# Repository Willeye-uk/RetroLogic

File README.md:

# **The RetroLogic 6502 SBC - KiCad 9 Files ([Ben Eater](https://eater.net/6502) Inspired)**

---

Welcome to the repository for the **KiCad 9 design files** of a single board computer (SBC) based on the classic **W65C02S microprocessor**. This project draws heavy inspiration from [Ben Eater's excellent 6502 computer series](https://eater.net/6502), expanding upon it with a range of features for greater versatility and modern connectivity.

## **Features**

This SBC design aims to provide a robust platform for learning and experimenting with the 6502. Key features include:

* **W65C02S Processor:** Capable of running up to **14 MHz**.
* **Memory:**
    * **62256 SRAM:** For fast read/write memory operations.
    * **28C256 EEPROM:** For storing your programs and firmware.
* **Input/Output:**
    * **65C22 Versatile Interface Adapter (VIA):** Provides programmable parallel I/O, timers, and shift registers.
    * **65C51 Asynchronous Communications Interface Adapter (ACIA):** For serial communication capabilities.
* **Connectivity:**
    * **DB9 Serial Port:** Standard serial connector for PC communication (via MAX232 level shifter).
    * **FTDI Breakout Serial Socket:** Convenient header for connecting an FTDI serial-to-USB adapter.
    * **SD Card Socket:** For mass storage, enabling easier program loading and data logging.
    * **LCD Screen Connector:** Directly interface with character LCDs.
* **Power & Expansion:**
    * **USB-B Power Socket:** Modern and widely available power input.
    * **Power Switch:** For easy power control.
    * **Crystal Socket:** Flexible clocking options, allowing for different crystal frequencies.
    * **Switchable Voltage for Add-ons:** Provides configurable power for external modules and expansion boards.
    * **Expansion Port:** Example diagnostic board included.
    
    * **Sound Card:** Expansion sound card and demo program.
    
    * **Terminal Card:** Expansion VGA terminal based on https://geoffg.net/terminal.html

## **Getting Started**

To explore or modify this design, you'll need **KiCad 9**.

**Clone this repository: \
** Bash \
git clone https://github.com/Willeye-uk/RetroLogic.git

1. 
2. **Open the project in KiCad 9:** Navigate to the cloned directory and open the `.kicad_pro` file.

From there, you can view the schematics, examine the PCB layout, and generate manufacturing files if you wish to build your own board. Or use the ones provided in Gerber Files dir.

## **Contributing**

Contributions are welcome! If you find issues, have suggestions for improvements, or want to add features, feel free to open an issue or submit a pull request.

## **License**

This project is open-source. Please refer to the `LICENSE` file (if present) for details.

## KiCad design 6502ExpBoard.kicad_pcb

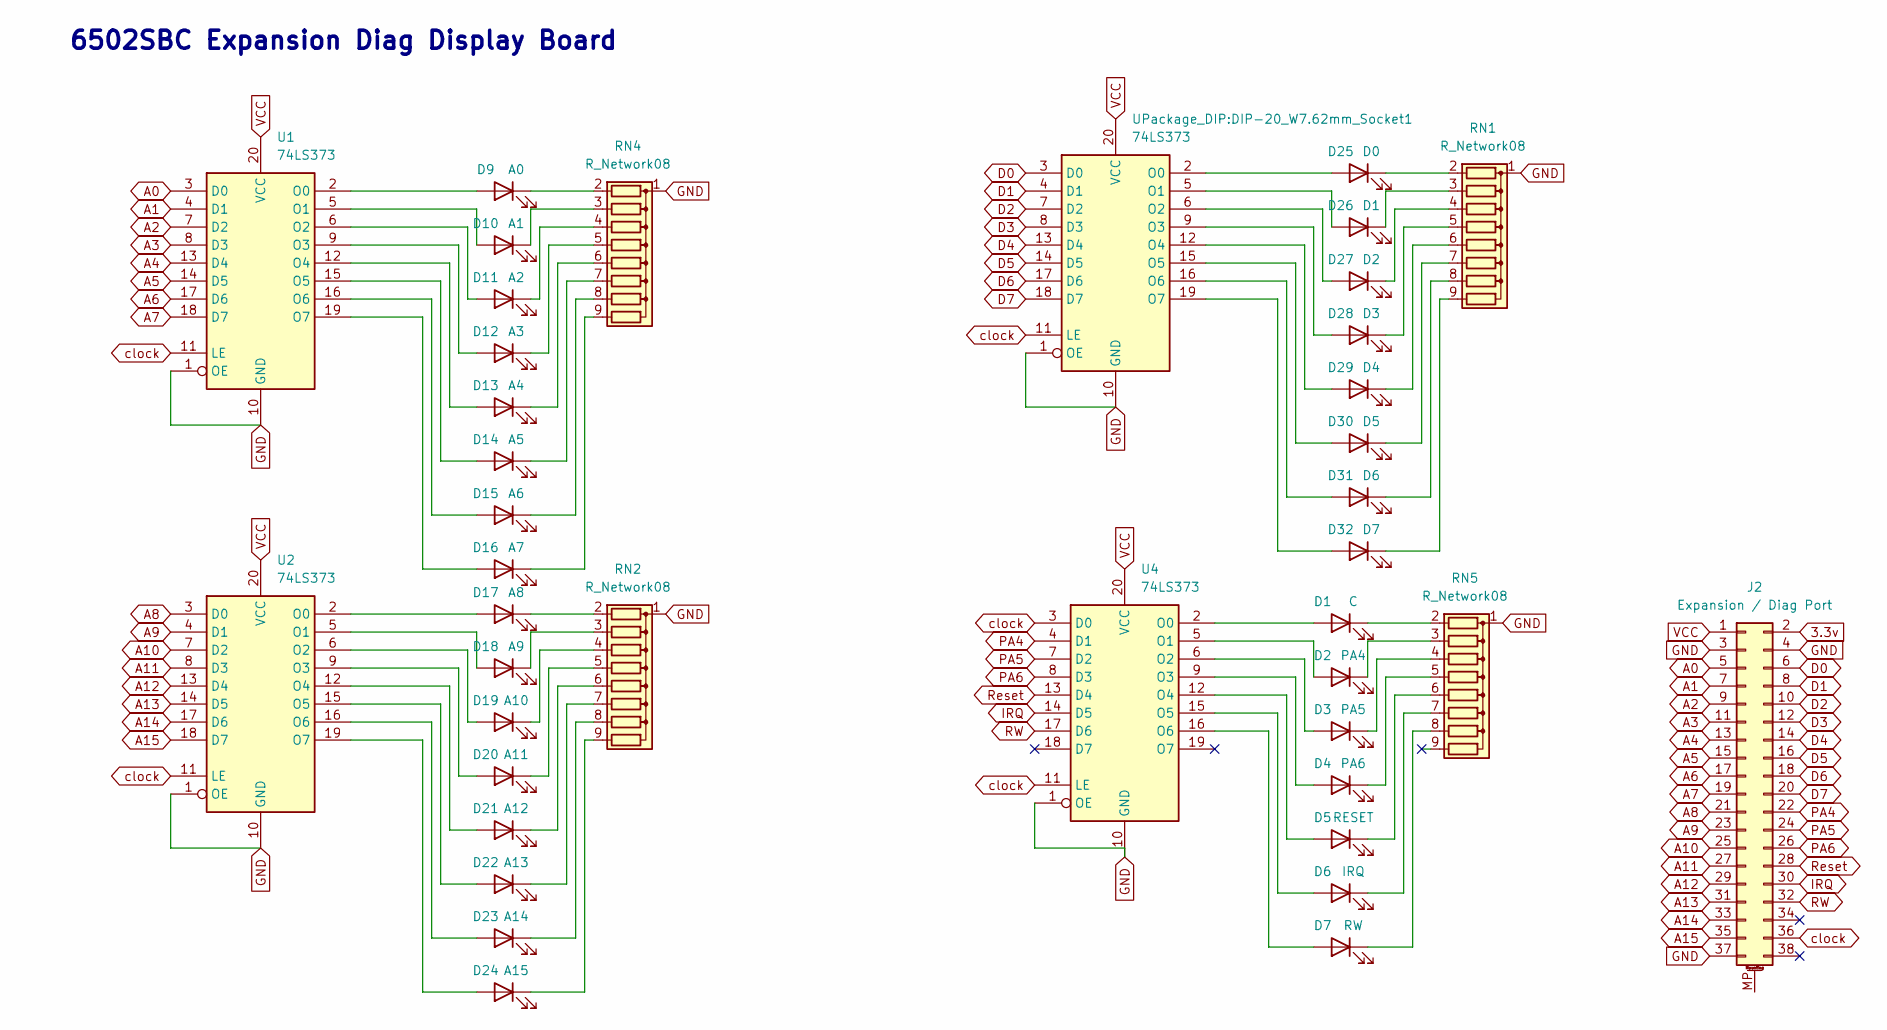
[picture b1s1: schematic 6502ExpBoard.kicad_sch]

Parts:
D1: C; LED_D3.0mm
D2: PA4; LED_D3.0mm
D3: PA5; LED_D3.0mm
D4: PA6; LED_D3.0mm
D5: RESET; LED_D3.0mm
D6: IRQ; LED_D3.0mm
D7: RW; LED_D3.0mm
D9: A0; LED_D3.0mm
D10: A1; LED_D3.0mm
D11: A2; LED_D3.0mm
D12: A3; LED_D3.0mm
D13: A4; LED_D3.0mm
D14: A5; LED_D3.0mm
D15: A6; LED_D3.0mm
D16: A7; LED_D3.0mm
D17: A8; LED_D3.0mm
D18: A9; LED_D3.0mm
D19: A10; LED_D3.0mm
D20: A11; LED_D3.0mm
D21: A12; LED_D3.0mm
D22: A13; LED_D3.0mm
D23: A14; LED_D3.0mm
D24: A15; LED_D3.0mm
D25: D0; LED_D3.0mm
D26: D1; LED_D3.0mm
D27: D2; LED_D3.0mm
D28: D3; LED_D3.0mm
D29: D4; LED_D3.0mm
D30: D5; LED_D3.0mm
D31: D6; LED_D3.0mm
D32: D7; LED_D3.0mm
J2: Expansion / Diag Port; PinHeader_2x19_P2.54mm_Vertical
RN1, RN2, RN4, RN5: R_Network08; R_Array_SIP9
U1, U2, U4: 74LS373; DIP-20_W7.62mm_Socket
UPackage_DIP:DIP-20_W7.62mm_Socket1: 74LS373; DIP-20_W7.62mm_Socket

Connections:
3.3v: J2.2
A0: J2.5, U1.3 (D0)
A1: J2.7, U1.4 (D1)
A2: J2.9, U1.7 (D2)
A3: J2.11, U1.8 (D3)
A4: J2.13, U1.13 (D4)
A5: J2.15, U1.14 (D5)
A6: J2.17, U1.17 (D6)
A7: J2.19, U1.18 (D7)
A8: J2.21, U2.3 (D0)
A9: J2.23, U2.4 (D1)
A10: J2.25, U2.7 (D2)
A11: J2.27, U2.8 (D3)
A12: J2.29, U2.13 (D4)
A13: J2.31, U2.14 (D5)
A14: J2.33, U2.17 (D6)
A15: J2.35, U2.18 (D7)
D0: J2.6, UPackage_DIP:DIP-20_W7.62mm_Socket1.3 (D0)
D1: J2.8, UPackage_DIP:DIP-20_W7.62mm_Socket1.4 (D1)
D2: J2.10, UPackage_DIP:DIP-20_W7.62mm_Socket1.7 (D2)
D3: J2.12, UPackage_DIP:DIP-20_W7.62mm_Socket1.8 (D3)
D4: J2.14, UPackage_DIP:DIP-20_W7.62mm_Socket1.13 (D4)
D5: J2.16, UPackage_DIP:DIP-20_W7.62mm_Socket1.14 (D5)
D6: J2.18, UPackage_DIP:DIP-20_W7.62mm_Socket1.17 (D6)
D7: J2.20, UPackage_DIP:DIP-20_W7.62mm_Socket1.18 (D7)
GND: J2.3, J2.4, J2.37, RN1.1 (common), RN2.1 (common), RN4.1 (common), RN5.1 (common), U1.1 (OE), U1.10 (GND), U2.1 (OE), U2.10 (GND), U4.1 (OE), U4.10 (GND), UPackage_DIP:DIP-20_W7.62mm_Socket1.1 (OE), UPackage_DIP:DIP-20_W7.62mm_Socket1.10 (GND)
IRQ: J2.30, U4.14 (D5)
unnamed: D1.2 (A), U4.2 (O0)
unnamed: D1.1 (K), RN5.2 (R1)
unnamed: D2.2 (A), U4.5 (O1)
unnamed: D2.1 (K), RN5.3 (R2)
unnamed: D3.2 (A), U4.6 (O2)
unnamed: D3.1 (K), RN5.4 (R3)
unnamed: D4.2 (A), U4.9 (O3)
unnamed: D4.1 (K), RN5.5 (R4)
unnamed: D5.2 (A), U4.12 (O4)
unnamed: D5.1 (K), RN5.6 (R5)
unnamed: D6.2 (A), U4.15 (O5)
unnamed: D6.1 (K), RN5.7 (R6)
unnamed: D7.2 (A), U4.16 (O6)
unnamed: D7.1 (K), RN5.8 (R7)
unnamed: D9.2 (A), U1.2 (O0)
unnamed: D9.1 (K), RN4.2 (R1)
unnamed: D10.2 (A), U1.5 (O1)
unnamed: D10.1 (K), RN4.3 (R2)
unnamed: D11.2 (A), U1.6 (O2)
unnamed: D11.1 (K), RN4.4 (R3)
unnamed: D12.2 (A), U1.9 (O3)
unnamed: D12.1 (K), RN4.5 (R4)
unnamed: D13.2 (A), U1.12 (O4)
unnamed: D13.1 (K), RN4.6 (R5)
unnamed: D14.2 (A), U1.15 (O5)
unnamed: D14.1 (K), RN4.7 (R6)
unnamed: D15.2 (A), U1.16 (O6)
unnamed: D15.1 (K), RN4.8 (R7)
unnamed: D16.2 (A), U1.19 (O7)
unnamed: D16.1 (K), RN4.9 (R8)
unnamed: D17.2 (A), U2.2 (O0)
unnamed: D17.1 (K), RN2.2 (R1)
unnamed: D18.2 (A), U2.5 (O1)
unnamed: D18.1 (K), RN2.3 (R2)
unnamed: D19.2 (A), U2.6 (O2)
unnamed: D19.1 (K), RN2.4 (R3)
unnamed: D20.2 (A), U2.9 (O3)
unnamed: D20.1 (K), RN2.5 (R4)
unnamed: D21.2 (A), U2.12 (O4)
unnamed: D21.1 (K), RN2.6 (R5)
unnamed: D22.2 (A), U2.15 (O5)
unnamed: D22.1 (K), RN2.7 (R6)
unnamed: D23.2 (A), U2.16 (O6)
unnamed: D23.1 (K), RN2.8 (R7)
unnamed: D24.2 (A), U2.19 (O7)
unnamed: D24.1 (K), RN2.9 (R8)
unnamed: D25.2 (A), UPackage_DIP:DIP-20_W7.62mm_Socket1.2 (O0)
unnamed: D25.1 (K), RN1.2 (R1)
unnamed: D26.2 (A), UPackage_DIP:DIP-20_W7.62mm_Socket1.5 (O1)
unnamed: D26.1 (K), RN1.3 (R2)
unnamed: D27.2 (A), UPackage_DIP:DIP-20_W7.62mm_Socket1.6 (O2)
unnamed: D27.1 (K), RN1.4 (R3)
unnamed: D28.2 (A), UPackage_DIP:DIP-20_W7.62mm_Socket1.9 (O3)
unnamed: D28.1 (K), RN1.5 (R4)
unnamed: D29.2 (A), UPackage_DIP:DIP-20_W7.62mm_Socket1.12 (O4)
unnamed: D29.1 (K), RN1.6 (R5)
unnamed: D30.2 (A), UPackage_DIP:DIP-20_W7.62mm_Socket1.15 (O5)
unnamed: D30.1 (K), RN1.7 (R6)
unnamed: D31.2 (A), UPackage_DIP:DIP-20_W7.62mm_Socket1.16 (O6)
unnamed: D31.1 (K), RN1.8 (R7)
unnamed: D32.2 (A), UPackage_DIP:DIP-20_W7.62mm_Socket1.19 (O7)
unnamed: D32.1 (K), RN1.9 (R8)
PA4: J2.22, U4.4 (D1)
PA5: J2.24, U4.7 (D2)
PA6: J2.26, U4.8 (D3)
RW: J2.32, U4.17 (D6)
Reset: J2.28, U4.13 (D4)
VCC: J2.1, U1.20 (VCC), U2.20 (VCC), U4.20 (VCC), UPackage_DIP:DIP-20_W7.62mm_Socket1.20 (VCC)
clock: J2.36, U1.11 (LE), U2.11 (LE), U4.3 (D0), U4.11 (LE), UPackage_DIP:DIP-20_W7.62mm_Socket1.11 (LE)

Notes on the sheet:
6502SBC Expansion Diag Display Board

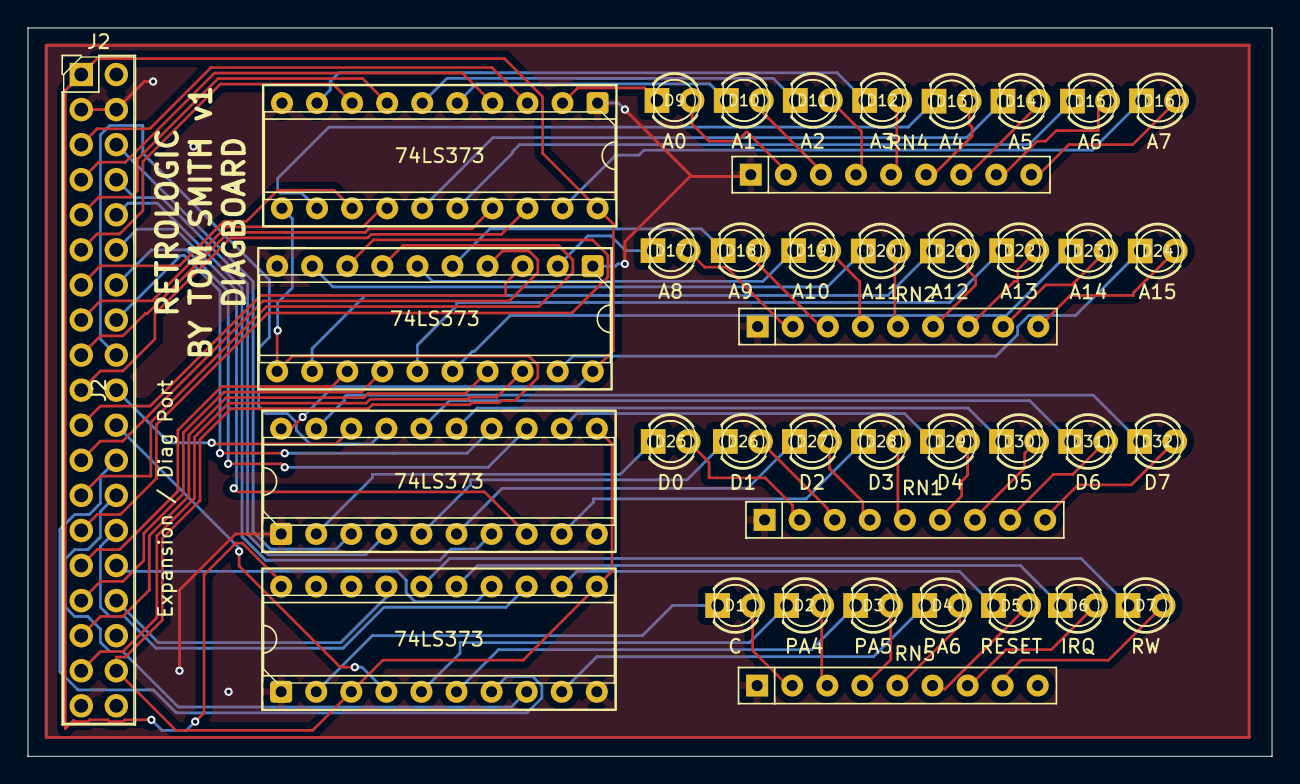
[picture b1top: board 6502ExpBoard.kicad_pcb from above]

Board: 2 copper layers, 90.1 x 52.8 mm, 40 parts (0 on the bottom side), 95 nets.

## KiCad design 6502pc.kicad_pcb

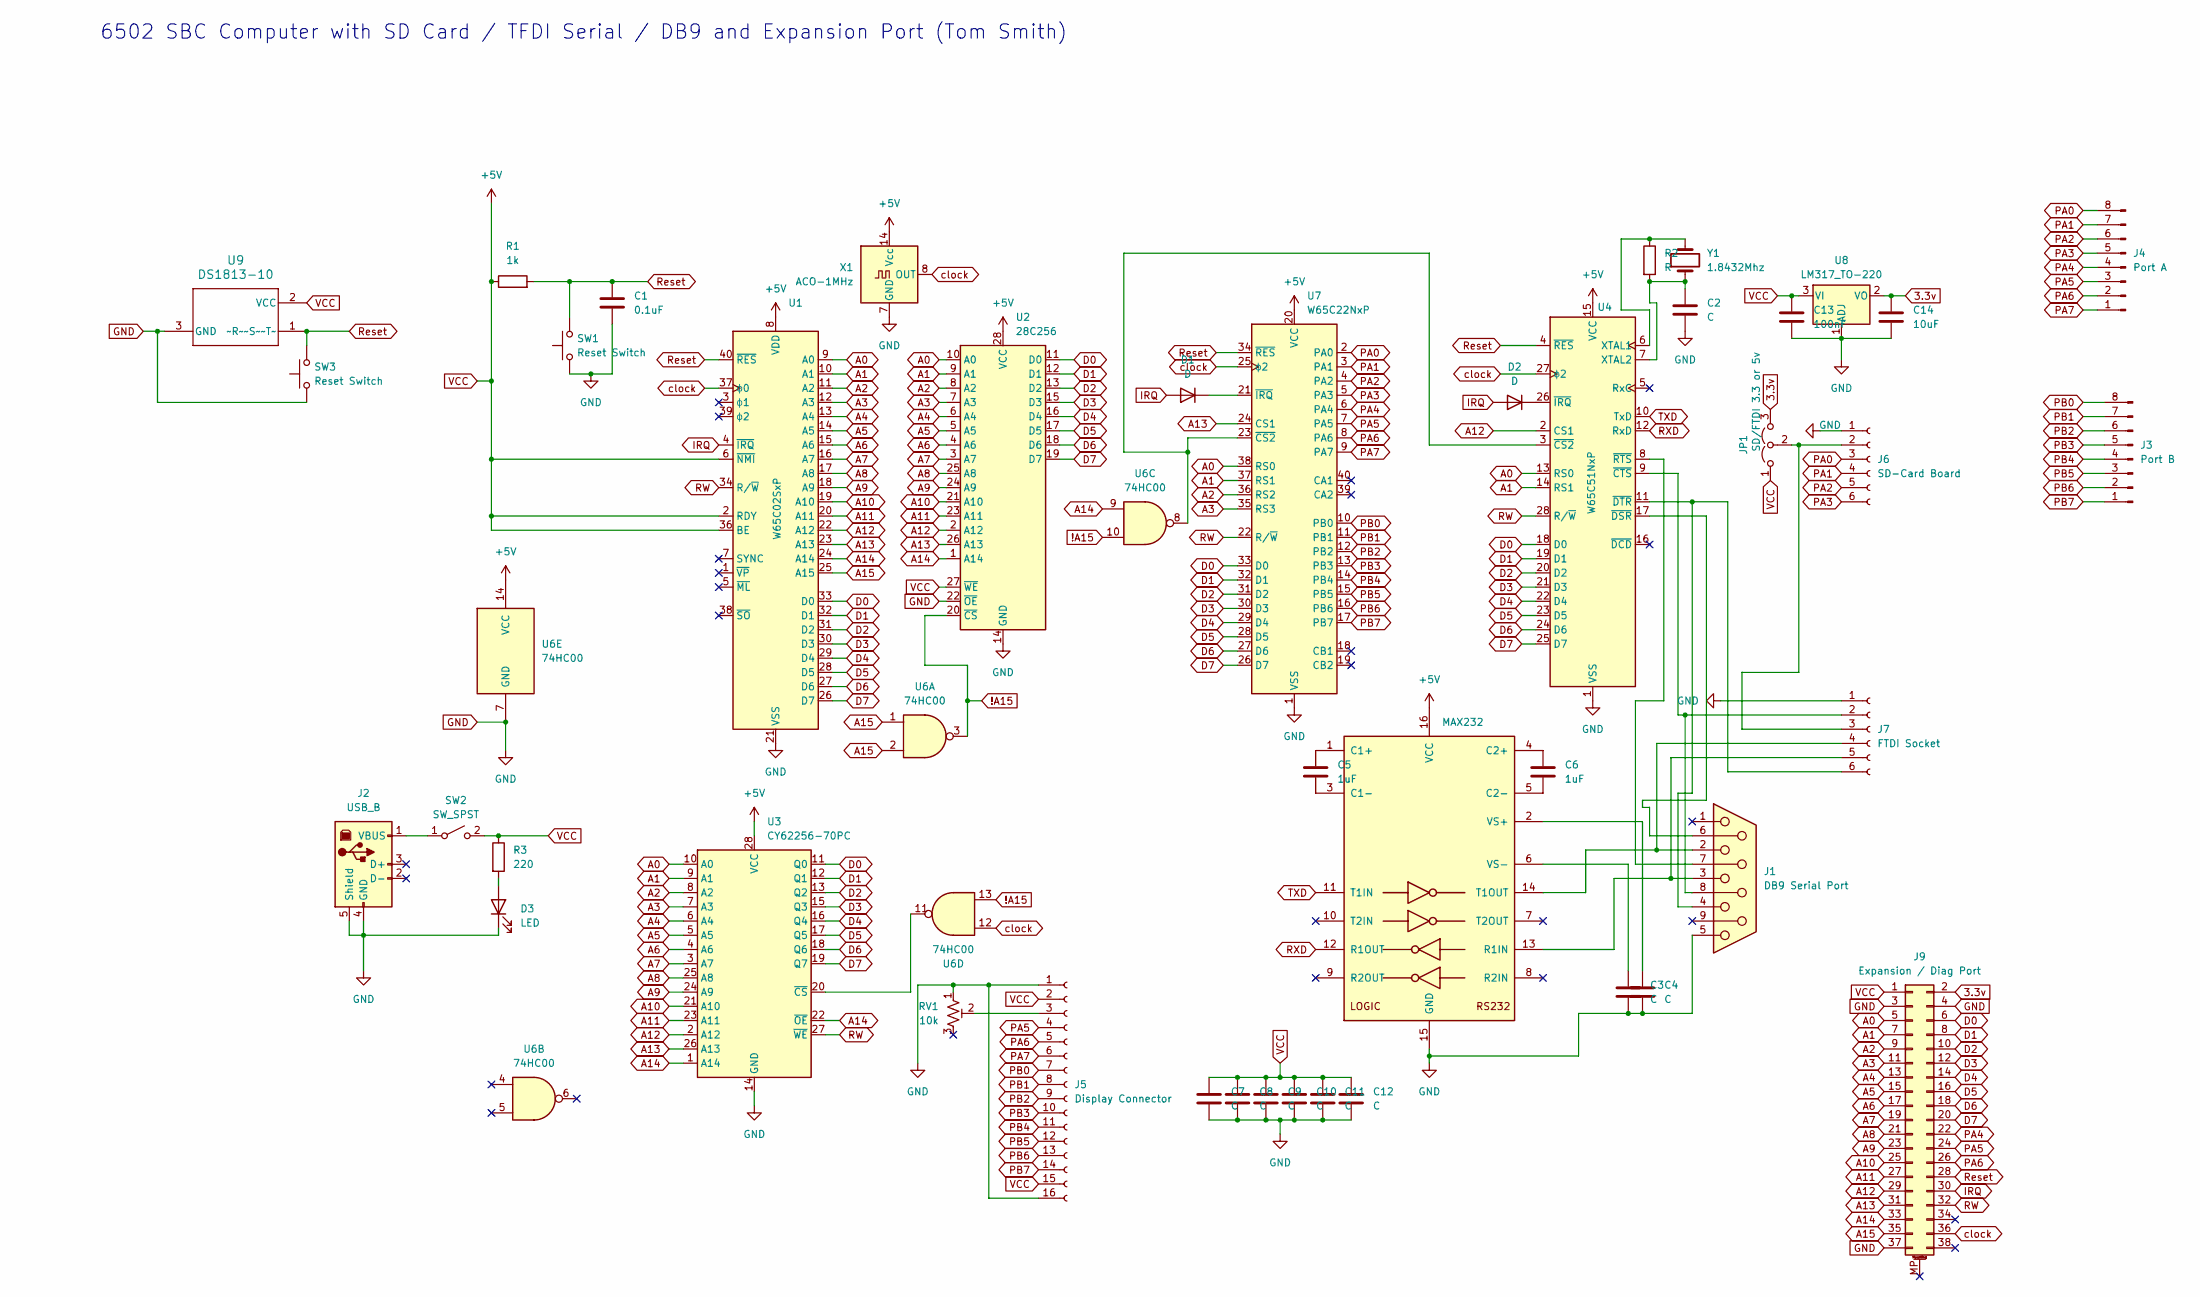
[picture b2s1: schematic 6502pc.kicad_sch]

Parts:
C1: 0.1uF; C_Disc_D10.0mm_W2.5mm_P5.00mm
C2, C3, C4, C7, C8, C9, C10, C11, C12: C; C_Disc_D10.0mm_W2.5mm_P5.00mm
C5, C6: 1uF; C_Disc_D10.0mm_W2.5mm_P5.00mm
C13: 100nF; C_Disc_D10.0mm_W2.5mm_P5.00mm
C14: 10uF; C_Disc_D10.0mm_W2.5mm_P5.00mm
D1, D2: D; R_Axial_DIN0204_L3.6mm_D1.6mm_P7.62mm_Horizontal
D3: LED; LED_D3.0mm
J1: DB9 Serial Port; DSUB-9_Female_Horizontal_P2.77x2.84mm_EdgePinOffset7.70mm_H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
J2: USB_B; USB_B_TE_5787834_Vertical
J3: Port B; PinSocket_1x08_P2.54mm_Vertical
J4: Port A; PinSocket_1x08_P2.54mm_Vertical
J5: Display Connector; PinSocket_1x16_P2.54mm_Vertical
J6: SD-Card Board; PinSocket_1x06_P2.54mm_Vertical
J7: FTDI Socket; PinSocket_1x06_P2.54mm_Vertical
J9: Expansion / Diag Port; PinSocket_2x19_P2.54mm_Vertical
JP1: SD/FTDI 3.3 or 5v; PinHeader_1x03_P2.54mm_Vertical
R1: 1k; R_Axial_DIN0204_L3.6mm_D1.6mm_P7.62mm_Horizontal
R2: R; R_Axial_DIN0204_L3.6mm_D1.6mm_P7.62mm_Horizontal
R3: 220; R_Axial_DIN0204_L3.6mm_D1.6mm_P7.62mm_Horizontal
RV1: 10k; Potentiometer_Bourns_3296X_Horizontal
SW1, SW3: Reset Switch; SW_PUSH_6mm
SW2: SW_SPST; SW_DIP_SPSTx01_Slide_9.78x4.72mm_W7.62mm_P2.54mm
U1: W65C02SxP; DIP-40_W15.24mm
U2: 28C256; DIP-28_W15.24mm
U3: CY62256-70PC; DIP-28_W15.24mm
U4: W65C51NxP; DIP-28_W15.24mm
U5: MAX232; DIP-16_W10.16mm
U6: 74HC00; DIP-14_W7.62mm
U7: W65C22NxP; DIP-40_W15.24mm
U8: LM317_TO-220; TO-220-3_Vertical
U9: DS1813-10; 21-0248A_MXM
X1: ACO-1MHz; Oscillator_DIP-14
Y1: 1.8432Mhz; Crystal_HC18-U_Vertical

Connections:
3.3v: C14.1, J9.2, JP1.3 (B), U8.2 (VO)
!A15: U2.20 (~CS), U6.3, U6.10, U6.13
A0: J9.5, U1.9 (A0), U2.10 (A0), U3.10 (A0), U4.13 (RS0), U7.38 (RS0)
A1: J9.7, U1.10 (A1), U2.9 (A1), U3.9 (A1), U4.14 (RS1), U7.37 (RS1)
A2: J9.9, U1.11 (A2), U2.8 (A2), U3.8 (A2), U7.36 (RS2)
A3: J9.11, U1.12 (A3), U2.7 (A3), U3.7 (A3), U7.35 (RS3)
A4: J9.13, U1.13 (A4), U2.6 (A4), U3.6 (A4)
A5: J9.15, U1.14 (A5), U2.5 (A5), U3.5 (A5)
A6: J9.17, U1.15 (A6), U2.4 (A6), U3.4 (A6)
A7: J9.19, U1.16 (A7), U2.3 (A7), U3.3 (A7)
A8: J9.21, U1.17 (A8), U2.25 (A8), U3.25 (A8)
A9: J9.23, U1.18 (A9), U2.24 (A9), U3.24 (A9)
A10: J9.25, U1.19 (A10), U2.21 (A10), U3.21 (A10)
A11: J9.27, U1.20 (A11), U2.23 (A11), U3.23 (A11)
A12: J9.29, U1.22 (A12), U2.2 (A12), U3.2 (A12), U4.2 (CS1)
A13: J9.31, U1.23 (A13), U2.26 (A13), U3.26 (A13), U7.24 (CS1)
A14: J9.33, U1.24 (A14), U2.1 (A14), U3.1 (A14), U3.22 (~OE), U6.9
A15: J9.35, U1.25 (A15), U6.1, U6.2
D0: J9.6, U1.33 (D0), U2.11 (D0), U3.11 (Q0), U4.18 (D0), U7.33 (D0)
D1: J9.8, U1.32 (D1), U2.12 (D1), U3.12 (Q1), U4.19 (D1), U7.32 (D1)
D2: J9.10, U1.31 (D2), U2.13 (D2), U3.13 (Q2), U4.20 (D2), U7.31 (D2)
D3: J9.12, U1.30 (D3), U2.15 (D3), U3.15 (Q3), U4.21 (D3), U7.30 (D3)
D4: J9.14, U1.29 (D4), U2.16 (D4), U3.16 (Q4), U4.22 (D4), U7.29 (D4)
D5: J9.16, U1.28 (D5), U2.17 (D5), U3.17 (Q5), U4.23 (D5), U7.28 (D5)
D6: J9.18, U1.27 (D6), U2.18 (D6), U3.18 (Q6), U4.24 (D6), U7.27 (D6)
D7: J9.20, U1.26 (D7), U2.19 (D7), U3.19 (Q7), U4.25 (D7), U7.26 (D7)
GND: C1.2, C2.2, C3.2, C4.2, C7.2, C8.2, C9.2, C10.2, C11.2, C12.2, C13.2, C14.2, D3.1 (K), J1.5, J2.4 (GND), J2.5 (Shield), J5.1, J5.16, J6.1, J7.1, J9.3, J9.4, J9.37, RV1.1, SW1.1, SW3.1, U1.21 (VSS), U2.14 (GND), U2.22 (~OE), U3.14 (GND), U4.1 (VSS), U5.15 (GND), U6.7 (GND), U7.1 (VSS), U8.1 (ADJ), U9.3 (GND), X1.7 (GND)
IRQ: D1.2 (A), D2.2 (A), J9.30, U1.4 (~IRQ)
unnamed: D1.1 (K), U7.21 (~IRQ)
unnamed: D2.1 (K), U4.26 (~IRQ)
unnamed: D3.2 (A), R3.2
unnamed: J2.1 (VBUS), SW2.1 (A)
unnamed: J5.3, RV1.2
unnamed: J6.2, J7.3, JP1.2 (C)
unnamed: J1.8, J7.2, U4.9 (~CTS)
unnamed: J1.2, J7.4, U5.14 (T1OUT)
unnamed: J1.3, J7.5, U5.13 (R1IN)
unnamed: J1.4, J7.6, U4.11 (~DTR)
unnamed: U3.20 (~CS), U6.11
unnamed: R2.1, U4.6 (XTAL1), Y1.2
unnamed: C2.1, R2.2, U4.7 (XTAL2), Y1.1
unnamed: U4.3 (~CS2), U6.8, U7.23 (~CS2)
unnamed: J1.6, U4.17 (~DSR)
unnamed: J1.7, U4.8 (~RTS)
unnamed: C5.1, U5.1 (C1+)
unnamed: C5.2, U5.3 (C1-)
unnamed: C6.1, U5.4 (C2+)
unnamed: C6.2, U5.5 (C2-)
unnamed: C4.1, U5.2 (VS+)
unnamed: C3.1, U5.6 (VS-)
PA0: J4.8, J6.3, U7.2 (PA0)
PA1: J4.7, J6.4, U7.3 (PA1)
PA2: J4.6, J6.5, U7.4 (PA2)
PA3: J4.5, J6.6, U7.5 (PA3)
PA4: J4.4, J9.22, U7.6 (PA4)
PA5: J4.3, J5.4, J9.24, U7.7 (PA5)
PA6: J4.2, J5.5, J9.26, U7.8 (PA6)
PA7: J4.1, J5.6, U7.9 (PA7)
PB0: J3.8, J5.7, U7.10 (PB0)
PB1: J3.7, J5.8, U7.11 (PB1)
PB2: J3.6, J5.9, U7.12 (PB2)
PB3: J3.5, J5.10, U7.13 (PB3)
PB4: J3.4, J5.11, U7.14 (PB4)
PB5: J3.3, J5.12, U7.15 (PB5)
PB6: J3.2, J5.13, U7.16 (PB6)
PB7: J3.1, J5.14, U7.17 (PB7)
RW: J9.32, U1.34 (R/~W), U3.27 (~WE), U4.28 (R/~W), U7.22 (R/~W)
RXD: U4.12 (RxD), U5.12 (R1OUT)
Reset: C1.1, J9.28, R1.2, SW1.2, SW3.2, U1.40 (~RES), U4.4 (~RES), U7.34 (~RES), U9.1 (~R~~S~~T~)
TXD: U4.10 (TxD), U5.11 (T1IN)
VCC: C7.1, C8.1, C9.1, C10.1, C11.1, C12.1, C13.1, J5.2, J5.15, J9.1, JP1.1 (A), R1.1, R3.1, SW2.2 (B), U1.2 (RDY), U1.6 (~NMI), U1.8 (VDD), U1.36 (BE), U2.27 (~WE), U2.28 (VCC), U3.28 (VCC), U4.15 (VCC), U5.16 (VCC), U6.14 (VCC), U7.20 (VCC), U8.3 (VI), U9.2 (VCC), X1.14 (Vcc)
clock: J9.36, U1.37 (ϕ0), U4.27 (ϕ2), U6.12, U7.25 (ϕ2), X1.8 (OUT)

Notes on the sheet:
6502 SBC Computer with SD Card / TFDI Serial / DB9 and Expansion Port (Tom Smith)

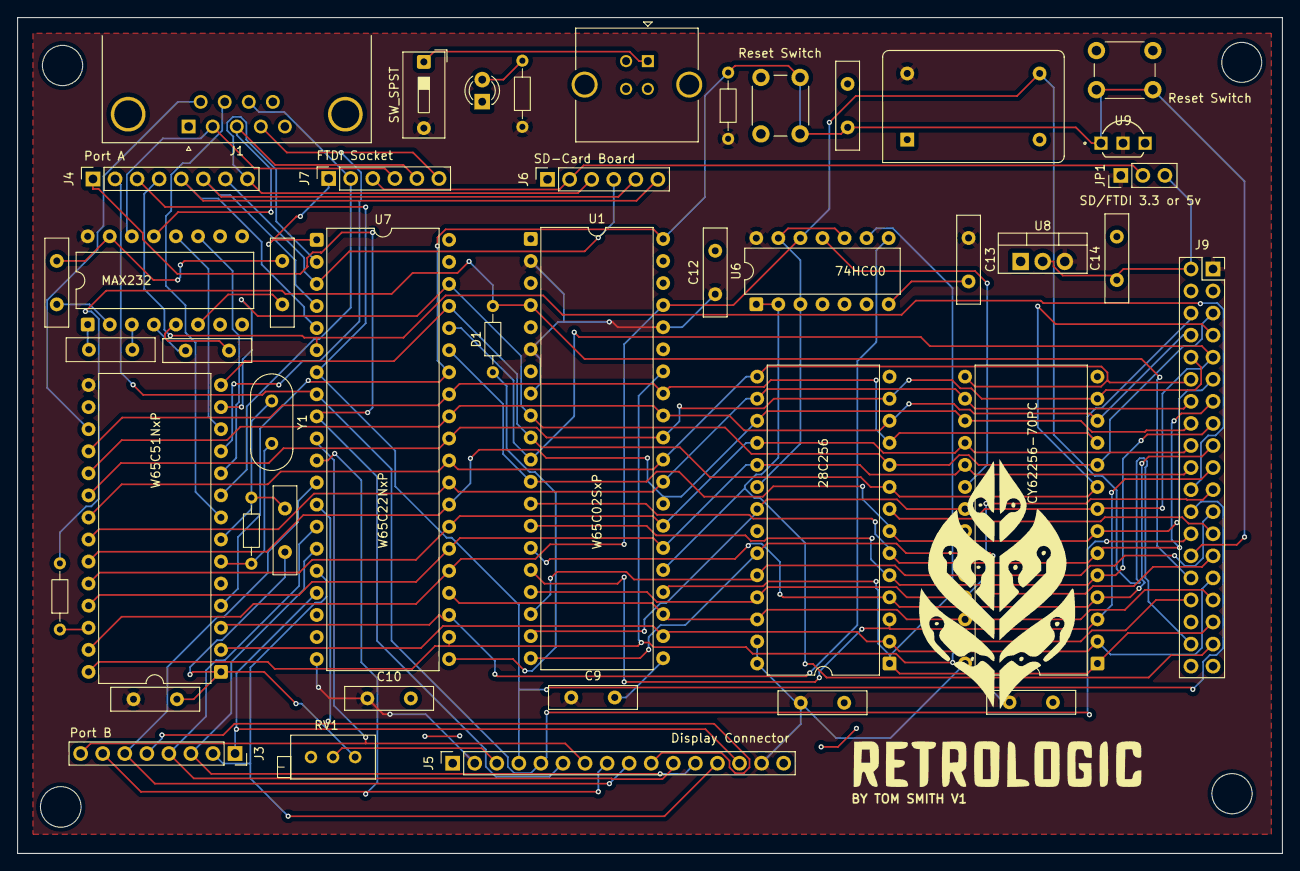
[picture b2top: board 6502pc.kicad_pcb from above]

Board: 2 copper layers, 145.6 x 96.2 mm, 44 parts (0 on the bottom side), 72 nets.

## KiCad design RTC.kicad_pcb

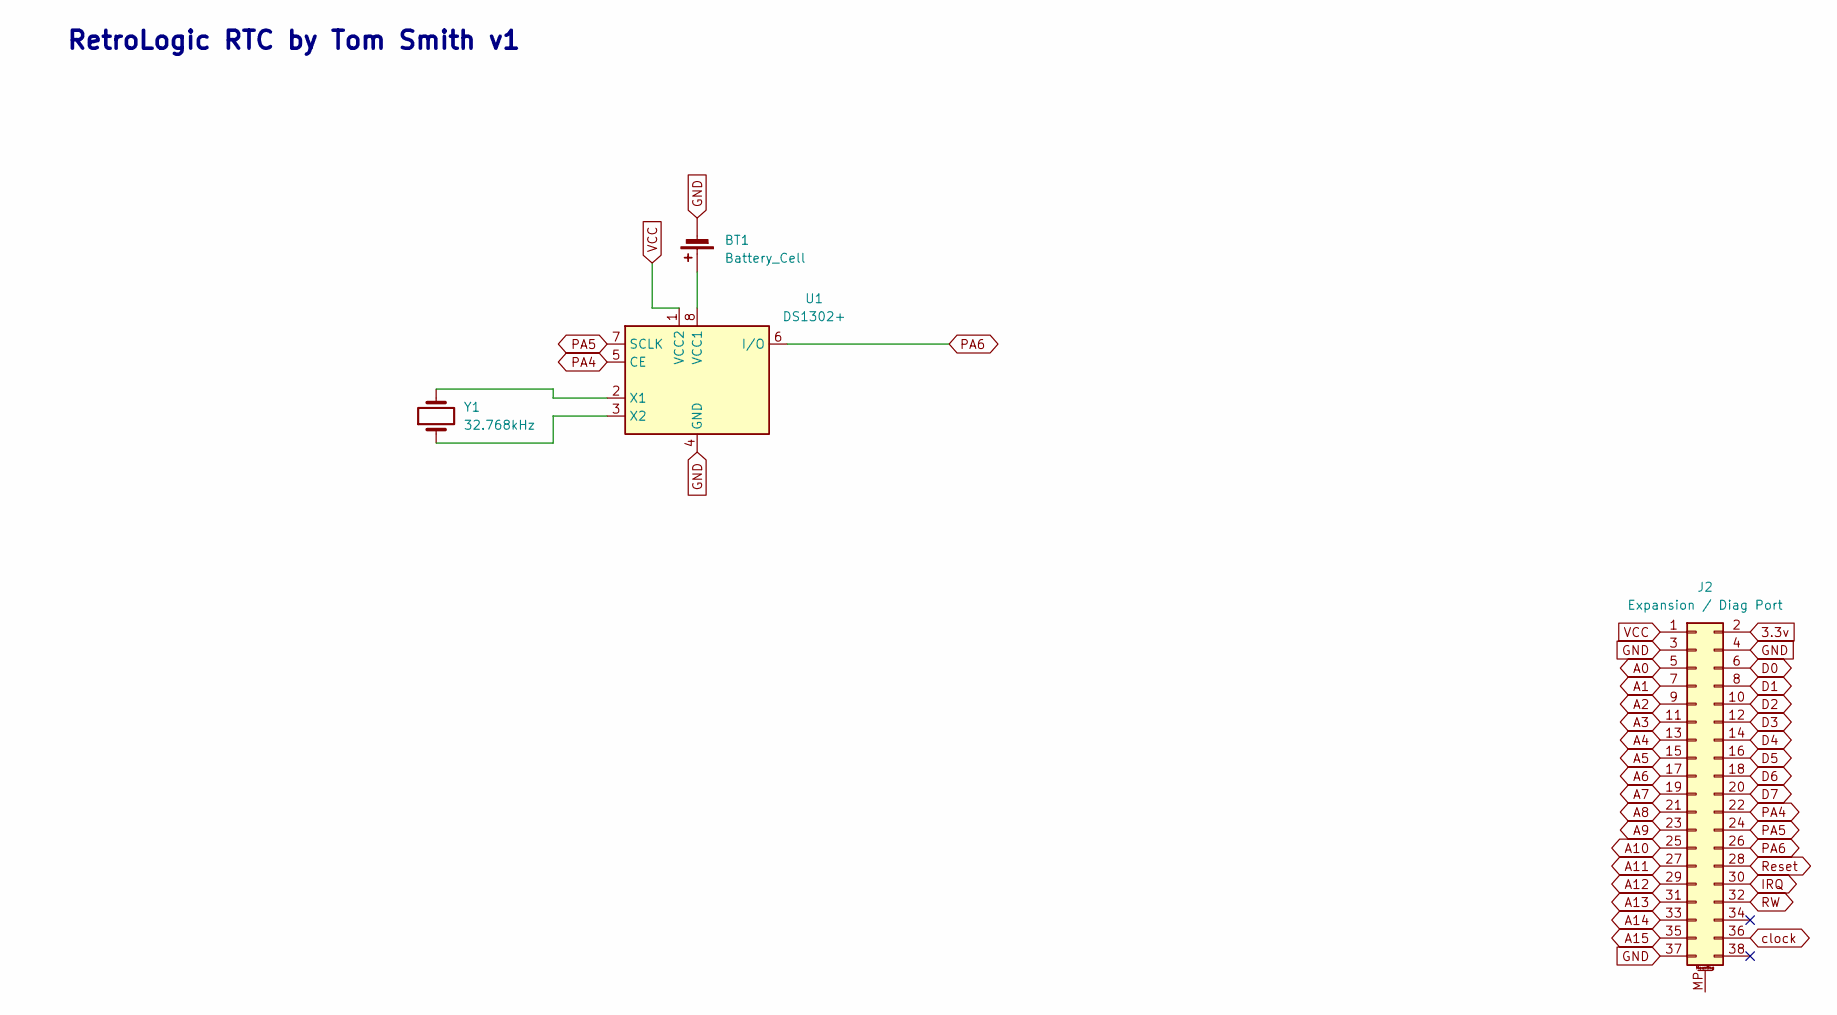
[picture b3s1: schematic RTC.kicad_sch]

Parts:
BT1: Battery_Cell; Battery_Panasonic_CR2032-HFN_Horizontal_CircularHoles
J2: Expansion / Diag Port; PinHeader_2x19_P2.54mm_Vertical
U1: DS1302+; DIP-8_W7.62mm
Y1: 32.768kHz; Crystal_DS15_D1.5mm_L5.0mm_Horizontal

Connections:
3.3v: J2.2
A0: J2.5
A1: J2.7
A2: J2.9
A3: J2.11
A4: J2.13
A5: J2.15
A6: J2.17
A7: J2.19
A8: J2.21
A9: J2.23
A10: J2.25
A11: J2.27
A12: J2.29
A13: J2.31
A14: J2.33
A15: J2.35
D0: J2.6
D1: J2.8
D2: J2.10
D3: J2.12
D4: J2.14
D5: J2.16
D6: J2.18
D7: J2.20
GND: BT1.2 (-), J2.3, J2.4, J2.37, U1.4 (GND)
IRQ: J2.30
unnamed: BT1.1 (+), U1.8 (VCC1)
unnamed: U1.2 (X1), Y1.2
unnamed: U1.3 (X2), Y1.1
PA4: J2.22, U1.5 (CE)
PA5: J2.24, U1.7 (SCLK)
PA6: J2.26, U1.6 (I/O)
RW: J2.32
Reset: J2.28
VCC: J2.1, U1.1 (VCC2)
clock: J2.36

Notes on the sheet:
RetroLogic RTC by Tom Smith v1

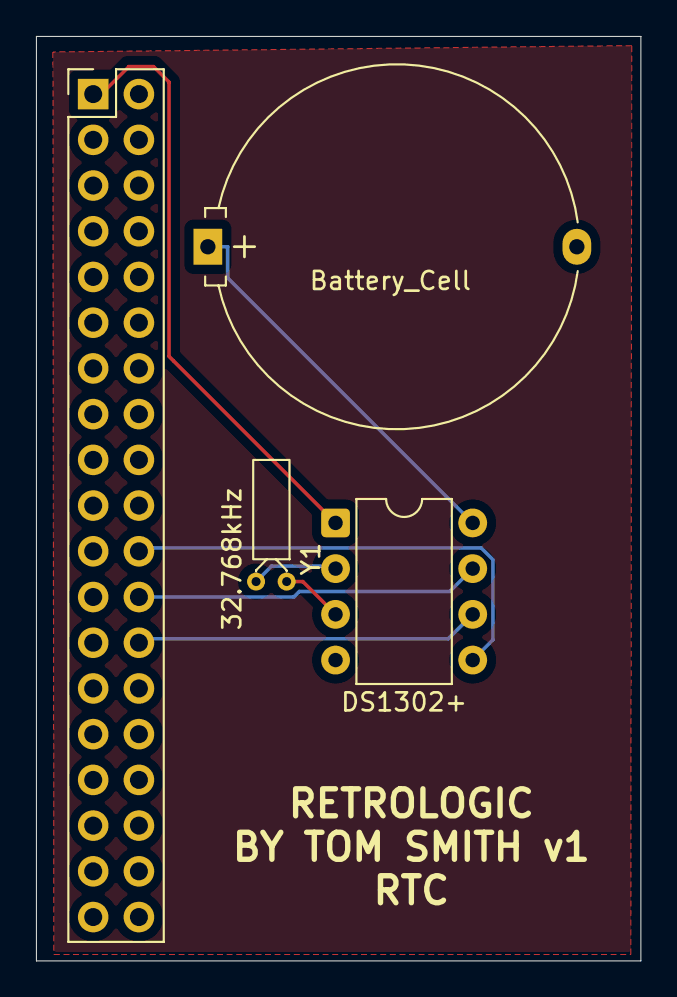
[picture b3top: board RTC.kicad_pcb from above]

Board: 2 copper layers, 33.6 x 51.4 mm, 4 parts (0 on the bottom side), 8 nets.

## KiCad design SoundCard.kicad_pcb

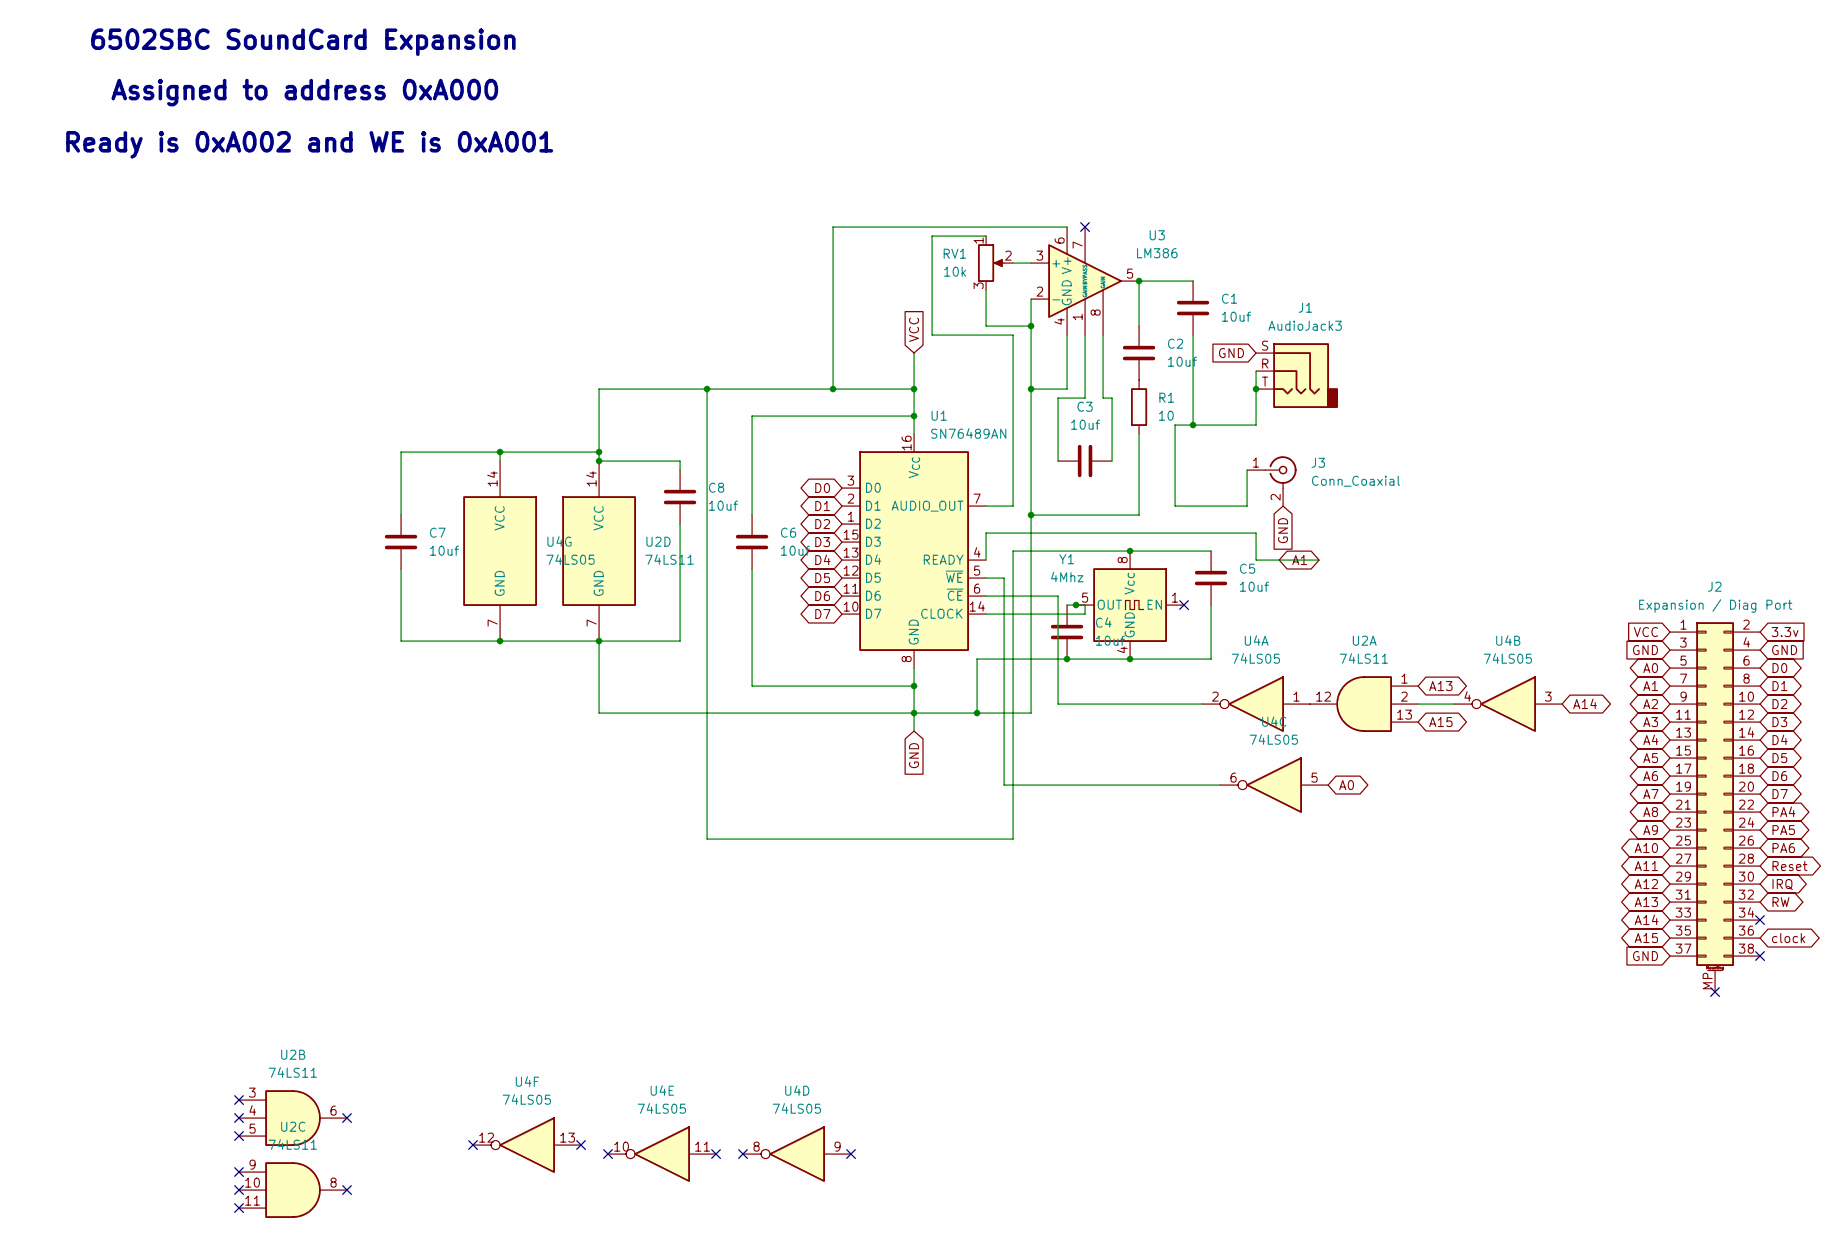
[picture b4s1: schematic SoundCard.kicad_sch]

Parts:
C1, C2: 10uf; R_Axial_DIN0204_L3.6mm_D1.6mm_P5.08mm_Horizontal
C3, C4, C5, C6, C7, C8: 10uf; C_Disc_D4.3mm_W1.9mm_P5.00mm
J1: AudioJack3; Jack_3.5mm_CUI_SJ1-3513N_Horizontal
J2: Expansion / Diag Port; PinHeader_2x19_P2.54mm_Vertical
J3: Conn_Coaxial; BNC_Amphenol_B6252HB-NPP3G-50_Horizontal
R1: 10; R_Axial_DIN0204_L3.6mm_D1.6mm_P5.08mm_Horizontal
RV1: 10k; Potentiometer_Bourns_3296W_Vertical
U1: SN76489AN; DIP-16_W7.62mm
U2: 74LS11; DIP-14_W7.62mm
U3: LM386; DIP-8_W7.62mm
U4: 74LS05; DIP-14_W7.62mm
Y1: 4Mhz; Oscillator_DIP-8

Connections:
3.3v: J2.2
A0: J2.5, U4.5
A1: J2.7, U1.4 (READY)
A2: J2.9
A3: J2.11
A4: J2.13
A5: J2.15
A6: J2.17
A7: J2.19
A8: J2.21
A9: J2.23
A10: J2.25
A11: J2.27
A12: J2.29
A13: J2.31, U2.1
A14: J2.33, U4.3
A15: J2.35, U2.13
D0: J2.6, U1.3 (D0)
D1: J2.8, U1.2 (D1)
D2: J2.10, U1.1 (D2)
D3: J2.12, U1.15 (D3)
D4: J2.14, U1.13 (D4)
D5: J2.16, U1.12 (D5)
D6: J2.18, U1.11 (D6)
D7: J2.20, U1.10 (D7)
GND: C4.1, C5.1, C6.1, C7.1, C8.1, J1.S, J2.3, J2.4, J2.37, J3.2 (Ext), R1.2, RV1.3, U1.8 (GND), U2.7 (GND), U3.2 (-), U3.4 (GND), U4.7 (GND), Y1.4 (GND)
IRQ: J2.30
unnamed: C1.1, C2.1, U3.5
unnamed: C2.2, R1.1
unnamed: C3.1, U3.1 (GAIN)
unnamed: C3.2, U3.8 (GAIN)
unnamed: C1.2, J1.R, J1.T, J3.1 (In)
unnamed: RV1.1, U1.7 (AUDIO_OUT)
unnamed: C4.2, U1.14 (CLOCK), Y1.5 (OUT)
unnamed: U1.6 (~CE), U4.2
unnamed: U1.5 (~WE), U4.6
unnamed: U2.2, U4.4
unnamed: U2.12, U4.1
unnamed: RV1.2, U3.3 (+)
PA4: J2.22
PA5: J2.24
PA6: J2.26
RW: J2.32
Reset: J2.28
VCC: C5.2, C6.2, C7.2, C8.2, J2.1, U1.16 (V_{CC}), U2.14 (VCC), U3.6 (V+), U4.14 (VCC), Y1.8 (Vcc)
clock: J2.36

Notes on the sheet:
Ready is 0xA002 and WE is 0xA001
Assigned to address 0xA000
6502SBC SoundCard Expansion

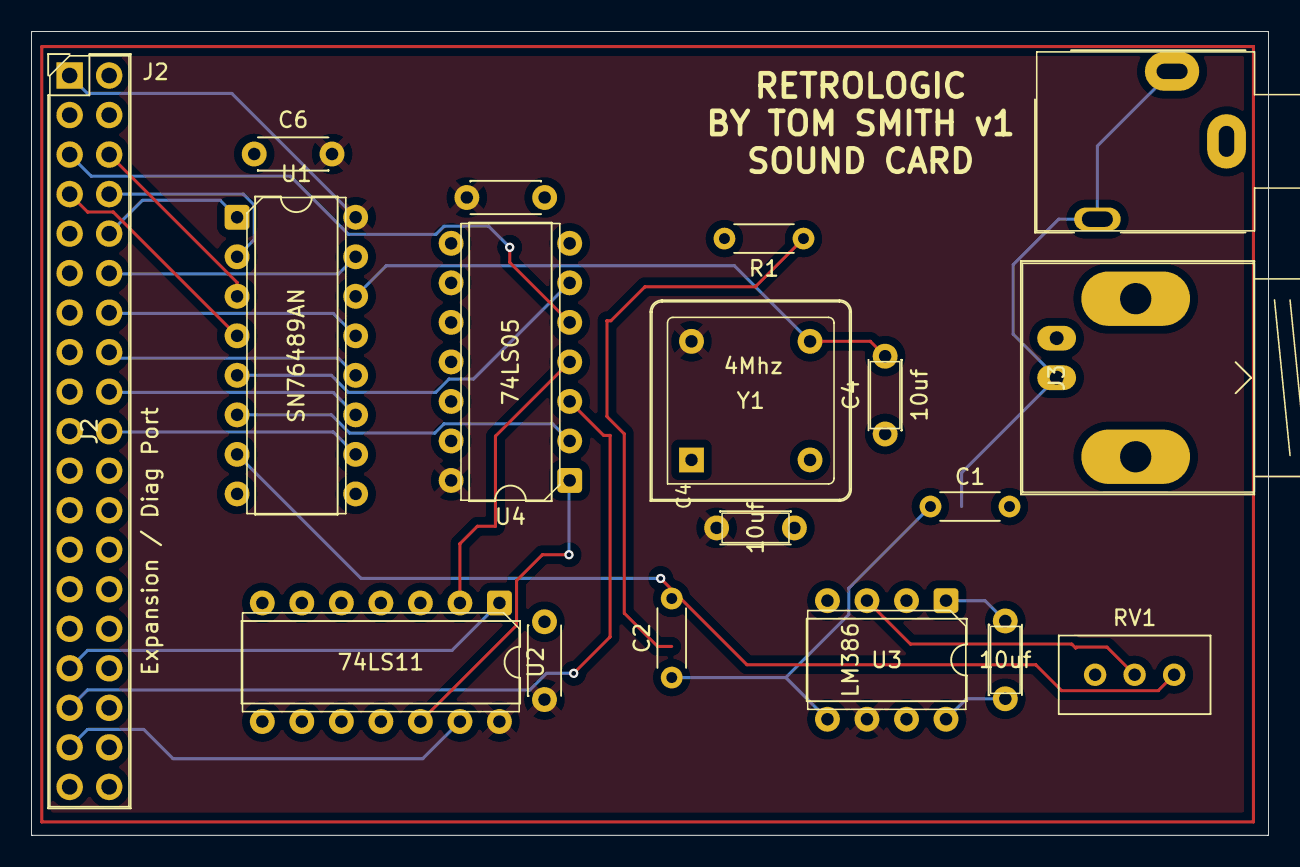
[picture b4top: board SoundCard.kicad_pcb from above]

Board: 2 copper layers, 79.5 x 51.7 mm, 18 parts (0 on the bottom side), 27 nets.

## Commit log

2025-06-01 First Version
2025-06-01 Git nore
2025-06-01 Git fix
2025-06-01 Added Expansion
2025-06-04 Restructure
2025-06-06 Add Sound Card
2025-06-08 Finished Sound Card
2025-06-09 Logos
2025-06-11 Routing and added auto reset
2025-06-11 More corrections
2025-06-11 bom and sound app
2025-06-13 Minor Changes
2025-06-13 readme
2025-06-16 Added RTC v1
2025-06-27 Terminal Card Addition
2025-06-27 Readme changes
2025-07-02 New circits
2025-07-02 terminalCard: Add PNG images for various components
2025-07-07 Diag Board led fixes
